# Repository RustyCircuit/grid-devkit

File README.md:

# Grid Devkit

KiCad PCB designed to interoperate with the [Intech Studio](https://github.com/intechstudio) Grid ecosystem. This devkit is a fork of [Intech's VSNX hardware design](https://github.com/intechstudio/grid-hardware/tree/master/Electrical/Design/PCBA-VSNX), adapted to fill a gap between fully-developed hardware and breadboard/DIY controller designs.

### KiCad Libraries

Custom libraries needed to be loaded into KiCad are found in [Intech's `grid-hardware` repo](https://github.com/intechstudio/grid-hardware).

### Firmware

The intended firmware for this devkit is found in [Intech's `grid-fw` repo](https://github.com/intechstudio/grid-fw).

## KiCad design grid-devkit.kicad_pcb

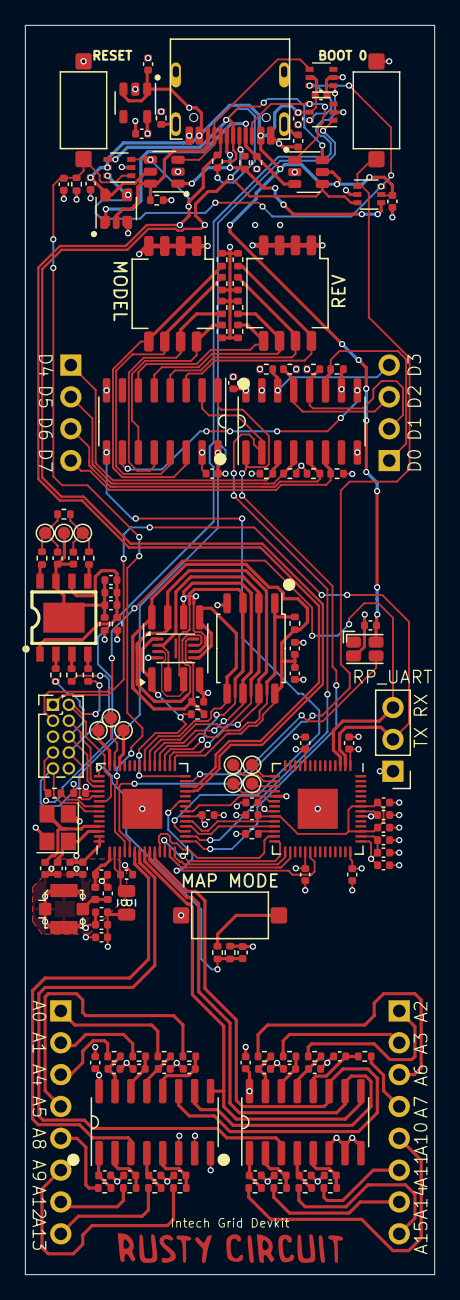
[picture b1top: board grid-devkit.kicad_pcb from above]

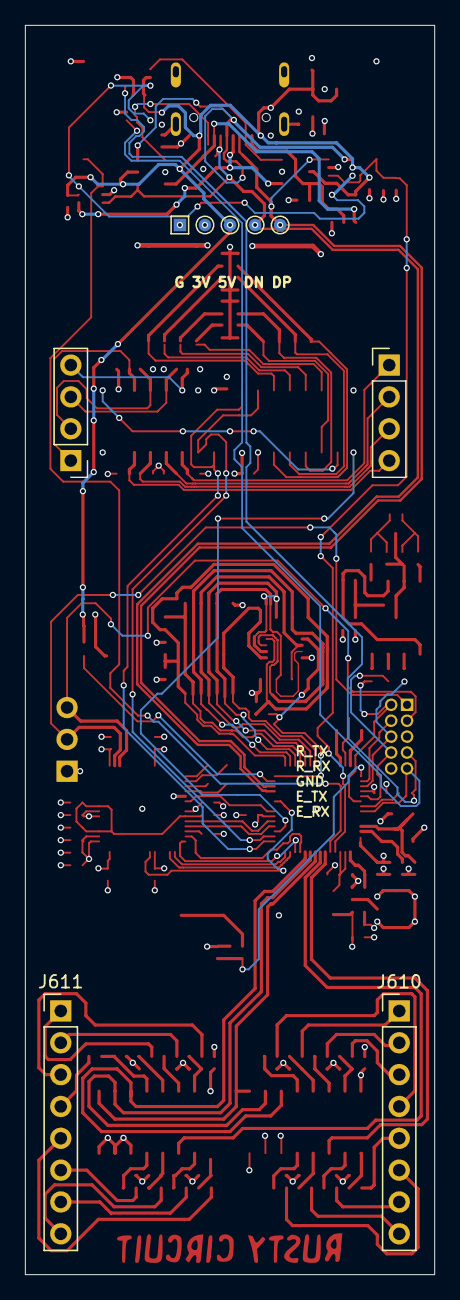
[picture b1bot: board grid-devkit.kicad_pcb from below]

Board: 4 copper layers, 32.7 x 99.7 mm, 165 parts (9 on the bottom side), 124 nets.

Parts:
C601: 4n7; CAP_0402
C602, C603, C733, C734, C746, C754, C755, C758, C937: 1u; CAP_0402
C604, C605, C606, C607, C608, C731, C732, C735, C736, C737, C738, C740, C741, C744, C745, C747, C749, C751, C752, C756, C757, C801, C901, C921, C936, C1001, C1002, C1003, C1004, C1005, C1006, C1007, C1008, C1009, C1010, C1011, C1012, C1013, C1014, C1015, C1016, C1017, C1018: 100n; CAP_0402
C739: 3p9; CAP_0402
C742: 1p8; CAP_0402
C743, C938: 10u; CAP_0402
C748, C750: 10p; CAP_0402
C753: 10n; CAP_0402
C939, C940: 1n; CAP_0402
D901: WS2812C-2020; UI_WS2812C-2020
J601: TYPE-C-32-M-12; USB_C_Korean_Hroparts_TYPE-C-31-M-12
J603, J604: Conn_01x04; PinHeader_1x04_P2.54mm_Vertical
J605: Conn_01x03; PinHeader_1x03_P2.54mm_Vertical
J610, J611: Conn_01x08; PinHeader_1x08_P2.54mm_Vertical
J701: C5137195; U.FL_Molex_MCRF_73412-0110_Vertical
J702: Conn_02x05_Odd_Even; PinHeader_2x05_P1.27mm_Vertical
L701: 1n8; IND_0402
L702: GZ2012D601TF; FERRIT_0805
L902, L903: BLM15AG102SN1D; FERRIT_0402
L904: BLM15PD121SN1D; FERRIT_0402
LOGO701: OSHWA
R601: 1M; RES_0402
R602, R603, R607, R608, R609, R610, R611, R612, R613, R614, R701, R729, R734, R735, R803, R804, R805, R806, R807, R808, R809, R810, R904: 5k1; RES_0402
R604, R605, R939: 0R; RES_0402
R606: 8R; RES_0402
R733, R736, R1001, R1002, R1003, R1004, R1005, R1006, R1007, R1008, R1009, R1010, R1011, R1012, R1013, R1014, R1015, R1016: 1k; RES_0402
R940, R941, R942: 33R; RES_0402
SW609: model_code; SW_DIP_SPSTx04_Slide_Copal_CHS-04B_W7.62mm_P1.27mm
SW610: rev_code; SW_DIP_SPSTx04_Slide_Copal_CHS-04B_W7.62mm_P1.27mm
SW701: C255807; SW_SPST_CK_RS282G05A3
SW702, SW703: C2905169; SW_SPST_CK_RS282G05A3
TP601: GND; TestPoint_Pad_1.0x1.0mm
TP602: UI; TestPoint_Pad_D1.0mm
TP603: VB; TestPoint_Pad_D1.0mm
TP604: D-; TestPoint_Pad_D1.0mm
TP605: D+; TestPoint_Pad_D1.0mm
TP701, TP702, TP703, TP704, TP901, TP902, TP903, TP904, TP905, TP906: TestPoint; TestPoint_Pad_D1.0mm
U601: LN1134A332MR-G; SOT-23-5
U602, U603: C5451661; SOT-23-6
U604: 74LVC1G08; SOT-23-5-AND-TSSOP5
U605, U606, U607, U608: BL1551B; SOT-363_SC-70-6
U609, U801: 74HC165; SOIC-16_74HC165
U610: APS1604M-3SQR-ZR; USON-8-1EP_3x2mm_P0.5mm_EP0.2x1.6mm
U703: RP2040; RP2040_QFN-56-1EP_7x7mm_P0.4mm_EP3.2x3.2mm
U704: ESP32-S3; QFN-56-1EP_7x7mm_P0.4mm_EP3.2x3.2mm
U705: W25Q64JVSSIQ; SOIC-8W_FLASH
U903: APS1604M-3SQR-SN; SOIC-8_3.9x4.9mm_P1.27mm
U918: NS4168_C910588; ESOP-8_L4.9-W3.9-P1.27-LS6.0-BL-EP
U1001, U1002: 74HC4051; SOIC-16_74HC4051
Y701: 40MHz; Crystal_SMD_Abracon_ABM8G-4Pin_3.2x2.5mm

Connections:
+1V1: C731.1, C732.1, C733.1, U703.23 (DVDD), U703.45 (VREG_VOUT), U703.50 (DVDD)
+3.3VA: C936.1, C937.1, C938.1, L904.1, U918.1 (CTRL), U918.6 (VDD)
+3V3: C603.2, C608.1, C734.1, C735.1, C736.1, C737.1, C738.1, C740.1, C741.1, C743.1, C744.1, C745.1, C746.1, C747.1, C751.1, C752.1, C753.1, C754.1, C757.2, C801.1, C1009.1, C1018.1, L702.2, L904.2, R607.2, R608.2, R609.2, R610.2, R611.2, R612.2, R613.2, R614.2, R701.1, R729.1, R735.1, SW609.1, SW609.2, SW609.3, SW609.4, SW610.1, SW610.2, SW610.3, SW610.4, TP602.1, U601.5 (OUT), U609.10 (SI), U609.16 (VCC), U703.1 (IOVDD), U703.10 (IOVDD), U703.22 (IOVDD), U703.33 (IOVDD), U703.42 (IOVDD), U703.43 (ADC_AVDD), U703.44 (VREG_IN), U703.48 (USB_VDD), U703.49 (IOVDD), U704.20 (VDD3P3_RTC), U704.46 (VDD3P3_CPU), U704.55 (VDDA1), U704.56 (VDDA2), U801.16 (VCC), U1001.16 (VDD), U1002.16 (VDD)
+5V: C602.1, C604.1, C605.1, C606.1, C607.1, C901.2, D901.4 (VDD), J601.A4B9 (VBUS), J601.A9B4 (VBUS), TP603.1, U601.1 (IN), U601.3 (EN), U602.5, U603.5, U604.5 (VCC), U605.5 (VCC), U606.5 (VCC), U607.5 (VCC), U608.5 (VCC)
/ANA_0: J610.1, R1001.2
/ANA_1: J610.2, R1005.2
/ANA_2: J611.1, R1009.2
/ANA_3: J611.2, R1013.2
/ANA_4: J610.3, R1002.2
/ANA_5: J610.4, R1006.2
/ANA_6: J611.3, R1010.2
/ANA_7: J611.4, R1014.2
/ANA_8: J610.5, R1003.2
/ANA_9: J610.6, R1007.2
/ANA_10: J611.5, R1011.2
/ANA_11: J611.6, R1015.2
/ANA_12: J610.7, R1004.2
/ANA_13: J610.8, R1008.2
/ANA_14: J611.7, R1012.2
/ANA_15: J611.8, R1016.2
/HWCFG/HWCFG_DATA: U704.17 (GPIO12), U801.9 (Q)
/LCDBUTTON/CLOCK: U609.2 (CLK), U704.16 (GPIO11), U801.2 (CLK)
/LCDBUTTON/D0: J604.1, R607.1, U609.11 (D0)
/LCDBUTTON/D1: J604.2, R608.1, U609.12 (D1)
/LCDBUTTON/D2: J604.3, R609.1, U609.13 (D2)
/LCDBUTTON/D3: J604.4, R610.1, U609.14 (D3)
/LCDBUTTON/D4: J603.1, R611.1, U609.3 (D4)
/LCDBUTTON/D5: J603.2, R612.1, U609.4 (D5)
/LCDBUTTON/D6: J603.3, R613.1, U609.5 (D6)
/LCDBUTTON/D7: J603.4, R614.1, U609.6 (D7)
/LCDBUTTON/DATA: U609.9 (Q), U801.10 (SI)
/LCDBUTTON/SHIFT: U609.1 (SH/~LD), U704.15 (GPIO10), U801.1 (SH/~LD)
/MCU/ESP_BOOT0: SW703.2 (B), U607.1 (A1), U704.5 (GPIO0)
/MCU/ESP_LNA: C742.1, L701.2, U704.1 (LNA_IN)
/MCU/ESP_RESET: C758.1, R735.2, SW702.2 (B), U608.1 (A1), U704.4 (CHIP_PU)
/MCU/LED_DATA_OUT: D901.3 (DIN), U704.27 (GPIO21)
/MCU/MAP_MODE: C757.1, R701.2, R736.2, U704.43 (GPIO38)
/MCU/RP_CLK: U703.20 (XIN), U704.21 (GPIO15)
/MCU/RP_INTERRUPT: U703.34 (GPIO22), U704.23 (GPIO17)
/MCU/RP_RUN: R729.2, U703.26 (RUN)
/MCU/RP_SPI0_CS: U703.28 (GPIO17), U704.12 (GPIO7)
/MCU/RP_SPI0_RX: U703.27 (GPIO16), U704.11 (GPIO6)
/MCU/RP_SPI0_SCK: U703.29 (GPIO18), U704.14 (GPIO9)
/MCU/RP_SPI0_TX: U703.30 (GPIO19), U704.13 (GPIO8)
/MCU/RP_SWCLK: U703.24 (SWCLK), U704.19 (GPIO14)
/MCU/RP_SWDIO: U703.25 (SWD), U704.18 (GPIO13)
/MCU/RP_UART0_RX: J605.3, J702.3, U703.3 (GPIO1)
/MCU/RP_UART0_TX: J605.2, J702.1, U703.2 (GPIO0)
/MCU/SPICLK: U610.6 (SCLK), U704.33 (GPIO30), U705.6 (CLK), U903.6 (SCLK)
/MCU/SPICS0: R734.2, U704.32 (GPIO29), U705.1 (~CS)
/MCU/SPICS1: R904.2, U610.1 (~CE), U704.28 (GPIO26), U903.1 (~CE)
/MCU/SPID: U610.5 (SI/SIO), U704.35 (GPIO32), U705.5 (DI(IO0)), U903.5 (SI/SIO)
/MCU/SPIHD: U610.7 (SIO3), U704.30 (GPIO27), U705.7 (IO3), U903.7 (SIO3)
/MCU/SPIQ: U610.2 (SO/SIO), U704.34 (GPIO31), U705.2 (DO(IO1)), U903.2 (SO/SIO)
/MCU/SPIWP: U610.3 (SIO2), U704.31 (GPIO28), U705.3 (IO2), U903.3 (SIO2)
/MCU/USB_DN: J601.B7 (D-), R604.1, TP604.1, U602.4, U607.3 (A2), U704.25 (GPIO19)
/MCU/USB_DP: J601.B6 (D+), R605.1, TP605.1, U603.4, U608.3 (A2), U704.26 (GPIO20)
/MCU/USB_POWER/A6: J601.A6 (D+), R605.2, U602.6, U608.4 (B)
/MCU/USB_POWER/A7: J601.A7 (D-), R604.2, U603.1, U607.4 (B)
/MCU/USB_POWER/CC1: J601.A5 (CC1), R602.1, U602.3, U604.1
/MCU/USB_POWER/CC2: J601.B5 (CC2), R603.1, U603.6, U604.2
/MCU/USB_POWER/DEBUG: U604.4, U605.6 (EN_A1), U606.6 (EN_A1), U607.6 (EN_A1), U608.6 (EN_A1)
/MCU/USB_POWER/SBU1: J601.A8 (SBU1), U603.3, U605.4 (B)
/MCU/USB_POWER/SBU2: J601.B8 (SBU2), U602.1, U606.4 (B)
ESP_GPIO_1: U704.6 (GPIO1), U1001.3 (X)
ESP_GPIO_2: U704.7 (GPIO2), U1002.3 (X)
ESP_GPIO_3: U704.8 (GPIO3), U1001.9 (C), U1002.9 (C)
ESP_GPIO_4: U704.9 (GPIO4), U1001.10 (B), U1002.10 (B)
ESP_GPIO_5: U704.10 (GPIO5), U1001.11 (A), U1002.11 (A)
ESP_GPIO_35: TP905.1, U704.40 (GPIO35)
ESP_GPIO_36: TP904.1, U704.41 (GPIO36)
ESP_GPIO_37: TP906.1, U704.42 (GPIO37)
ESP_GPIO_39: J702.4, U704.44 (GPIO39)
ESP_GPIO_40: J702.6, R940.1, U704.45 (GPIO40)
ESP_GPIO_41: J702.8, R941.1, U704.47 (GPIO41)
ESP_GPIO_42: J702.2, R942.1, U704.48 (GPIO42)
ESP_GPIO_43: J702.7, R733.2, U605.1 (A1)
ESP_GPIO_44: J702.9, U606.1 (A1), U704.50 (GPIO44)
GND: C601.2, C602.2, C603.1, C604.2, C605.2, C606.2, C607.2, C608.2, C731.2, C732.2, C733.2, C734.2, C735.2, C736.2, C737.2, C738.2, C739.2, C740.2, C741.2, C742.2, C743.2, C744.2, C745.2, C746.2, C747.2, C748.2, C749.2, C750.2, C751.2, C752.2, C753.2, C754.2, C755.2, C756.2, C758.2, C801.2, C901.1, C921.2, C1001.2, C1002.2, C1003.2, C1004.2, C1005.2, C1006.2, C1007.2, C1008.2, C1009.2, C1010.2, C1011.2, C1012.2, C1013.2, C1014.2, C1015.2, C1016.2, C1017.2, C1018.2, D901.2 (VSS), J601.A1B12 (GND), J601.A12B1 (GND), J605.1, J701.2 (Ext), J702.5, R601.2, R602.2, R603.2, R803.2, R804.2, R805.2, R806.2, R807.2, R808.2, R809.2, R810.2, R939.1, SW701.2 (B), SW702.1 (A), SW703.1 (A), TP601.1, U601.2 (GND), U602.2, U603.2, U604.3 (GND), U605.2 (GND), U606.2 (GND), U607.2 (GND), U608.2 (GND), U609.8 (GND), U609.15 (INH), U610.4 (VSS), U703.19 (TESTEN), U703.57 (GND), U704.57 (GND), U705.4 (GND), U801.8 (GND), U801.15 (INH), U903.4 (VSS), U1001.6 (Inh), U1001.7 (VEE), U1001.8 (VSS), U1002.6 (Inh), U1002.7 (VEE), U1002.8 (VSS), Y701.2, Y701.4
GNDA: C936.2, C937.2, C938.2, C939.2, C940.2, R939.2, TP903.1, U918.7 (GND), U918.9 (EP)
unnamed: C601.1, J601.S1 (SHIELD)
unnamed: C749.1, L702.1, U704.2 (VDD3P3), U704.3 (VDD3P3)
unnamed: C939.1, L903.2, R606.2, TP902.1
unnamed: C940.1, L902.1, R606.1, TP901.1
unnamed: J601.S2 (SHIELD), R601.1
unnamed: C739.1, J701.1 (In), L701.1
unnamed: R736.1, SW701.1 (A)
unnamed: TP701.1, U703.15 (GPIO12)
unnamed: TP702.1, U703.16 (GPIO13)
unnamed: TP703.1, U703.17 (GPIO14)
unnamed: TP704.1, U703.18 (GPIO15)
unnamed: R733.1, U704.49 (GPIO43)
unnamed: C750.1, U704.53 (XTAL_N), Y701.3
unnamed: C748.1, U704.54 (XTAL_P), Y701.1
unnamed: R806.1, SW609.8, U801.11 (D0)
unnamed: R805.1, SW609.7, U801.12 (D1)
unnamed: R804.1, SW609.6, U801.13 (D2)
unnamed: R803.1, SW609.5, U801.14 (D3)
unnamed: R807.1, SW610.8, U801.3 (D4)
unnamed: R808.1, SW610.7, U801.4 (D5)
unnamed: R809.1, SW610.6, U801.5 (D6)
unnamed: R810.1, SW610.5, U801.6 (D7)
unnamed: R941.2, U918.3 (BCLK)
unnamed: R940.2, U918.2 (LRCLK)
unnamed: R942.2, U918.4 (SDATA)
unnamed: L903.1, U918.5 (VON)
unnamed: L902.2, U918.8 (VOP)
unnamed: C1001.1, R1001.1, U1001.13 (X0)
unnamed: C1005.1, R1005.1, U1001.14 (X1)
unnamed: C1002.1, R1002.1, U1001.15 (X2)
unnamed: C1006.1, R1006.1, U1001.12 (X3)
unnamed: C1003.1, R1003.1, U1001.1 (X4)
unnamed: C1007.1, R1007.1, U1001.5 (X5)
unnamed: C1004.1, R1004.1, U1001.2 (X6)
unnamed: C1008.1, R1008.1, U1001.4 (X7)
unnamed: C1010.1, R1009.1, U1002.13 (X0)
unnamed: C1014.1, R1013.1, U1002.14 (X1)
unnamed: C1011.1, R1010.1, U1002.15 (X2)
unnamed: C1015.1, R1014.1, U1002.12 (X3)
unnamed: C1012.1, R1011.1, U1002.1 (X4)
unnamed: C1016.1, R1015.1, U1002.5 (X5)
unnamed: C1013.1, R1012.1, U1002.2 (X6)
unnamed: C1017.1, R1016.1, U1002.4 (X7)
VDD_SPI: C755.1, C756.1, C921.1, R734.1, R904.1, U610.8 (VCC), U704.29 (VDD_SPI), U705.8 (VCC), U903.8 (VCC)

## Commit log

2025-05-13 Adds traces
2025-05-24 SUKU antenna and xtal layout done
2025-05-25 SUKU mcu positioning and grids fixed, decoupling capacitors placed and routed
2025-05-25 SUKU memory layout optimized
2025-06-08 SUKU analog layout grid alignment fixed, mcu connection routed
2025-08-02 Removes unused refs, adjusts size, and adds traces for LED, boot, and reset
2025-08-02 Adds traces for shift registers
2025-09-04 Adds image to README
2025-09-04 Updates F.Silkscreen
2025-09-04 SUKU workflopw files added
2025-09-04 SUKU design files moved to subdirectory to allow matrix workflow to run
